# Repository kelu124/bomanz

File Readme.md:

# Module: A high speed ADC for the RaspberryPi

The board in red:

## Description

### What is it supposed to do?

I've always needed a small upgrade to the existing raspberry ADC extensions, would love something in the 20-Msps range. Let's see if one can do it! Never tried smd, and thinking of using both smd and dip.. interesting learning curve ahead.

I've tried 3 different versions, increasing in complexity

* An older version using a [CA3306](/CA3306E/) can be found as well: going around 10Msps, 6 bits. DIP based components.
* A possibly [fast version of a 8 bit AD08200 ADC](/ADC08200/) is available, going up to 12Msps. 
* The latest [24Msps pHAT](/AD9200v2/)

### Image of these HATs

## Some results

### 24 Msps with the latest version

Details and FFT of a signal at 1.9MHz

### 11 Msps with the previous

FFT of a signal at 1.9MHz

### Testing a 1MHz signal with the CA3306

Imaging a 1MHz sine:

## License

### Bomanz 

The [echOmods project](https://github.com/kelu124/echomods) and its prototypes (so Bomanz) are open hardware, and working with open-hardware components.

Licensed under TAPR Open Hardware License (www.tapr.org/OHL)

Copyright Kelu124 (kelu124@gmail.com ) 2015-2018

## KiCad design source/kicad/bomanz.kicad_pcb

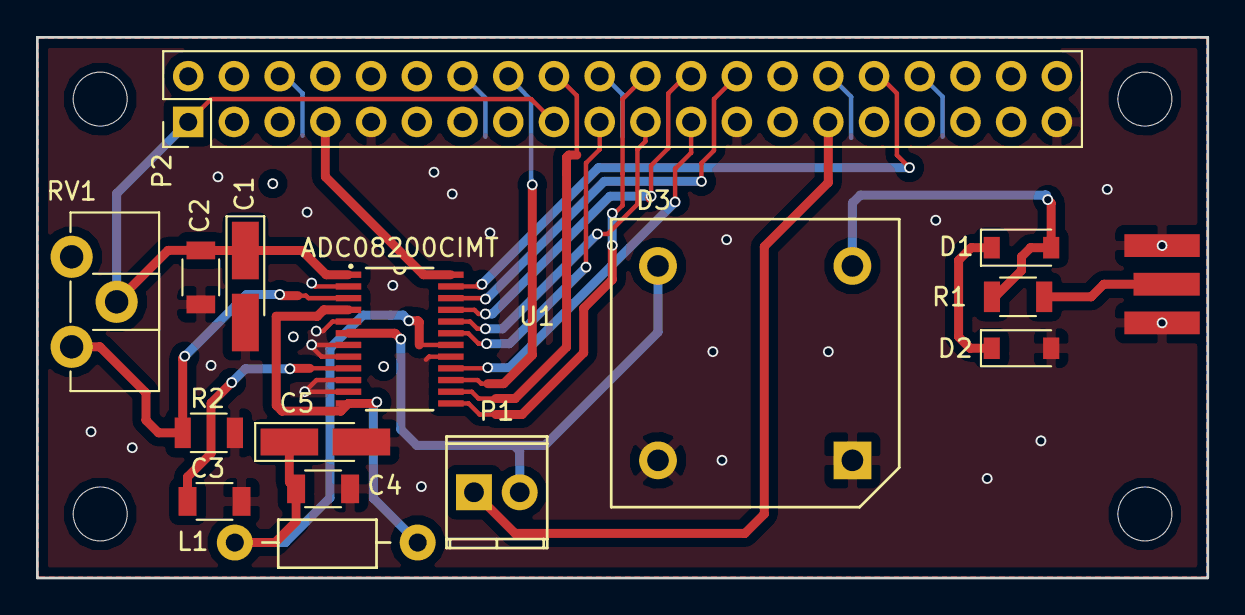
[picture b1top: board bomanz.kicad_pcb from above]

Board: 2 copper layers, 65.0 x 30.0 mm, 15 parts (0 on the bottom side), 19 nets.

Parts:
C1, C5: CP_Tantalum_Case-A_EIA-3216-18_Hand
C2, C3, C4: C_1206
D1, D2: D_SOD-123
D3: Diode_Bridge_15.7x15.7
L1: Choke_Horizontal_RM10mm
P1: TerminalBlock_Pheonix_MPT-2.54mm_2pol
P2: Pin_Header_Straight_2x20_Pitch2.54mm
R1, R2: R_1206
RV1: Potentiometer_Trimmer_ACP_CA9h2.5_Vertical_Px2.5mm_Py5.0mm
U1: ADC08200CIMT; ADC08200_PW_24

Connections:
+3V3: C1.1, C2.1, L1.1, P2.1, P2.17, RV1.2, U1.1, U1.4, U1.12
CLK: P2.7, U1.24
D0: P2.26, U1.22
D1: P2.24, U1.21
D2: P2.21, U1.20
D3: P2.19, U1.19
D4: P2.23, U1.16
D5: P2.16, U1.15
D6: P2.18, U1.14
D7: P2.22, U1.13
DM: P2.32, U1.23
GND: C1.2, C2.2, C3.2, C4.2, C5.2, D2.2, D3.2, D3.3, P2.6, P2.9, P2.14, P2.20, P2.25, P2.30, P2.34, P2.39, R2.2, U1.2, U1.5, U1.7, U1.8, U1.10, U1.11, U1.17
IN: P1.1, P2.29
unnamed: C3.1, U1.9
unnamed: C4.1, C5.1, L1.2, U1.18
unnamed: D1.1, D2.1
unnamed: D1.2, D3.4, R1.1
unnamed: D3.1, P1.2, U1.6
unnamed: R2.1, RV1.3, U1.3

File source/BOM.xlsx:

Sr. No. | Designator | Description | Package | Quantity | URL | Part No.
1 | P2 | Pin Header Straight 2x20 Pitch2.54mm | 2x20 DIP 2.54 mm Pitch | 1 | http://www.digikey.com/product-detail/en/ amphenol-fci/10046971-003LF/609-2859-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 | 10046971-003LF
2 | U1 | ADC08200 24 Pin | TSSOP | 1 | http://www.digikey.com/product-detail/ en/texas-instruments/ADC08200CIMT-NOPB/A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 | ADC08200CIMT/NOPB-ND
3 | C1,C5 | Capacitor Tantalum 10uF | 1206 | 2 | http://www.digikey.com/products/ en?keywords=399-3684-2-ND | 399-3684-2-ND
4 | C2,C3,C4 | Capacitor 0.1uF | 1206 | 3 | http://www.digikey.com/products /en?keywords=399-1249-2-ND | 399-1249-2-ND
5 | D1,D2 | Zener Diode | SOD-123 | 2 | http://www.digikey.com/products /en?keywords=mmsz5221b-fditr-nd | MMSZ5221B-FDITR-ND
6 | D3 | Diode Bridge rectifier | 4-Square, D-72 (15.7 x15.7) | 1 | http://www.digikey.com/products/ en?keywords=vs-kbpc802pbfgi-nd | VS-KBPC802PBFGI-ND
7 | L1 | Choke | Axial (0.236" Dia x 0.394" L (5.99mm x 10.01mm)) | 1 | http://www.digikey.com/ products/en?keywords=M2204-ND | M2204-ND
8 | P1 | Pin Header Straight 1x2 Pitch2.54mm | 1x2 DIP 2.54 mm Pitch | 1 | http://www.digikey.com/products/ en?keywords=sam9523-nd | SAM9523-ND
9 | R1 | Resistor 220 Ohms | 1206 | 1 | http://www.digikey.com/ products/en?keywords=311-220frtr-nd | 311-220FRTR-ND
10 | R2 | Ressitor 100 Ohms | 1206 | 1 | http://www.digikey.com/product-detail/ en/yageo/RC1206FR-07100RL/311-100FRTR-ND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 | 311-100FRTR-ND
11 | RV1 | Potentiometer | Mounting Hole Square - 0.276" x 0.276" Face x 0.228" L (7.00mm x 7.00mm x 5.80m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 | 1 | http://www.digikey.com/products/ en?keywords=CT6ep202-ND | CT6EP202-ND
12 |  | SMA Edge Connector | Board Edge, End Launch | 1 | http://www.digikey.com/ products/en?keywords=ACX1652-ND | ACX1652-ND

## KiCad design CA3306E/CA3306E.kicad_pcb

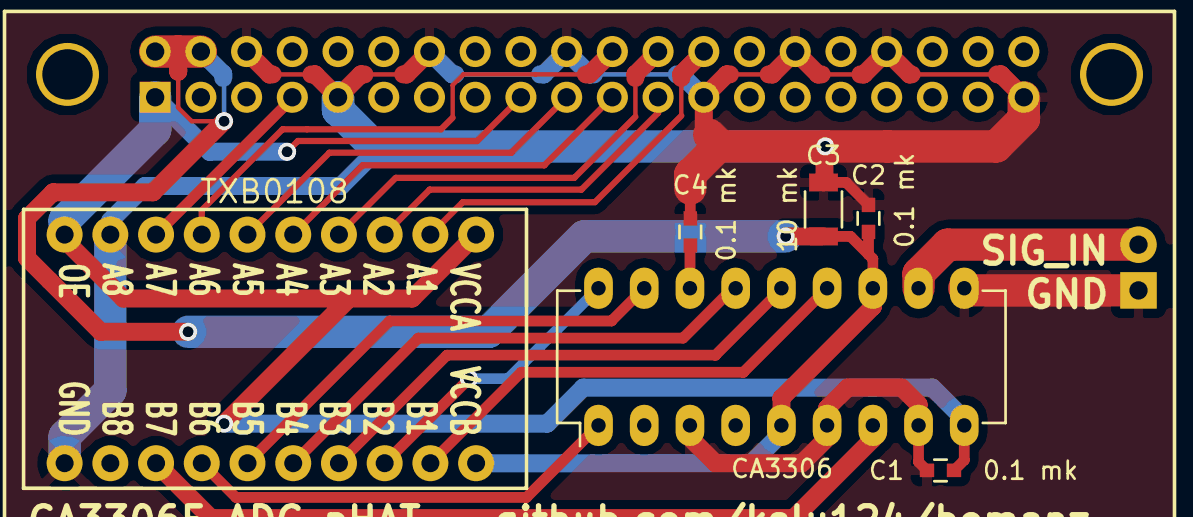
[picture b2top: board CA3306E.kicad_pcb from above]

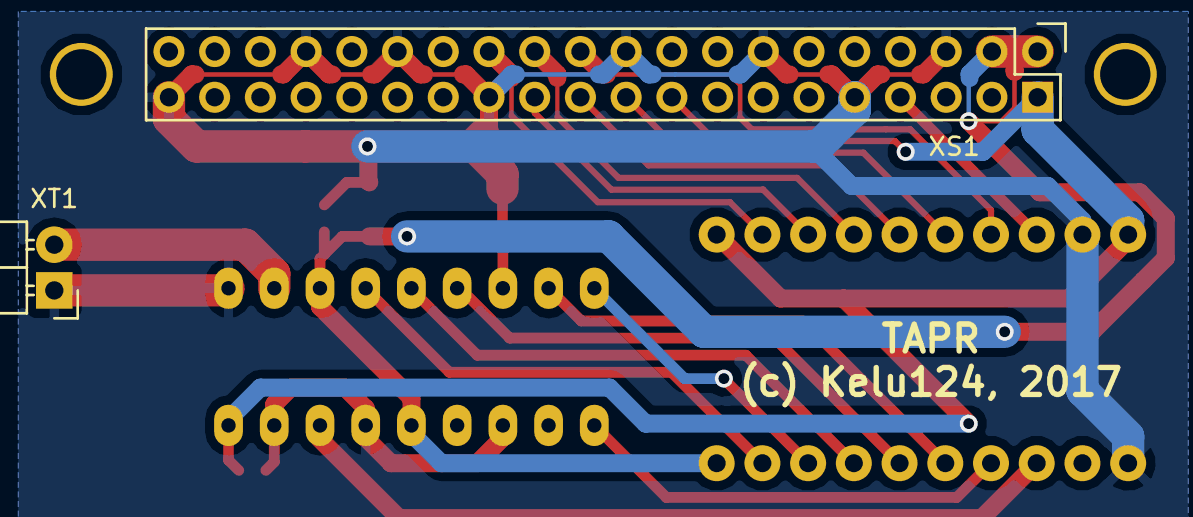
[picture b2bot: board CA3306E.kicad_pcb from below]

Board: 2 copper layers, 8 parts (2 on the bottom side), 19 nets.

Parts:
C1, C2, C4: 0.1 mk; C_0603
C3: 10 mk; C_1206
CA3306: DIP-18_W7.62mm_LongPads
TXB0108: MountingHole_6mm_Pad
XS1: Pin_Header_Straight_2x20
XT1: Pin_Header_Angled_1x02

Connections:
B1: CA3306.13, TXB0108.19
B2: CA3306.14, TXB0108.17
B3: CA3306.15, TXB0108.16
B4: CA3306.17, TXB0108.15
B5: CA3306.18, TXB0108.18
B6: CA3306.1, TXB0108.14
C4_P: C4.1, CA3306.16
CLK: CA3306.7, TXB0108.13
GND: C1.2, C2.2, C3.2, C4.2, CA3306.3, CA3306.6, CA3306.8, CA3306.10, TXB0108.9, TXB0108.11, XS1.6, XS1.9, XS1.14, XS1.20, XS1.25, XS1.30, XS1.34, XS1.39, XT1.1
GPIO4: TXB0108.8, XS1.7
GPIO7: TXB0108.2, XS1.26
GPIO8: TXB0108.4, XS1.24
GPIO9: TXB0108.5, XS1.21
GPIO10: TXB0108.6, XS1.19
GPIO11: TXB0108.3, XS1.23
GPIO25: TXB0108.7, XS1.22
SIG_IN: CA3306.11, XT1.2
VDD_3V3: C1.1, CA3306.9, TXB0108.1, TXB0108.10, XS1.1, XS1.17
VDD_5V: C2.1, C3.1, CA3306.5, CA3306.12, TXB0108.20, XS1.2, XS1.4

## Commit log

2017-03-20 First Bomanz commit ;)
2017-03-20 KiCad sources
2017-03-20 Adding gerbers/drill
2017-03-25 Add Gerbers CA3306
2017-03-26 Adding the CA3306E board
2017-04-06 Adding PCBs images
2017-04-12 Adding the mounted boards pics
2017-04-18 Adding CA3306E code
2017-04-18 Adding link to worklog
2017-04-19 Adding previous compiling error
2017-04-19 ADding EE-October-1991
2017-04-22 First samples of CA3306
2017-04-22 Adding JPG images
2017-04-23 Adding Freq review
2017-04-30 Adding tests with ADC08200
2017-04-30 Some FFT processing
2017-04-30 Adding offsetter + analyse
2017-04-30 Adding JPG
2017-05-01 Adding filters on piezo without backing
2017-05-01 Adding bivi's method
2017-05-01 Adding VRef tests and enveloppe detection comparison
2017-05-01 Adding Comparison with Croaker
2017-05-01 Updating Bomanz Readme
2017-05-07 Adding updated kernel code
2017-05-13 Some style cleaning. I can not clean the entire file because I would have to modify some macro and I do not want to modify them without testing them before
2017-05-15 Pins layout
2017-05-18 Adding a dual AD9200 pHAT
2017-05-18 Adding AD9200s readme
2017-05-22 Adding Doj v2
2017-05-22 Adding berkAltium files
2017-06-04 Autopush
2017-07-19 Adding the 24Msps version of the ADC pHAT
2017-07-19 Adding pics of different protos
2017-08-09 Last file
2019-12-30 Make compatible with kitspace.org

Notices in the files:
parts and their libraries:
Copyright 2016 Accelerated Designs. All rights reserved.
